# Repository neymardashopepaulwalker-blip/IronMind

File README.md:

# IronMind Macropad

Um macropad customizado com 6 switches mecânicos, encoder rotativo e display OLED, desenvolvido do zero como projeto de aprendizado em CAD, programação e design de PCB.

---

## Sobre o Projeto

Criei esse macropad para desenvolver minhas habilidades em três áreas que sempre quis dominar: design de PCB no KiCad, modelagem 3D no Fusion 360 e programação de firmware com KMK/CircuitPython. O resultado ficou muito bom, mesmo com alguns erros no caminho — e aprendi muito com cada um deles!

---

## Funcionalidades

| Tecla | Função |
|---|---|
| SW1 | Abre Claude (claude.ai) |
| SW2 | Abre Jarvis (site pessoal) |
| SW3 | Abre Discord |
| SW4 | Música anterior |
| SW5 | Play / Pause |
| SW6 | Próxima música |
| Encoder (girar) | Volume + / - |
| Encoder (pressionar) | Mute |
| OLED | Mostra volume e info |

---

## Lista de Materiais (BOM)

| Componente | Quantidade |
|---|---|
| Seeeduino XIAO RP2040 | 1x |
| Switch Cherry MX | 6x |
| Rotary Encoder EC11 | 1x |
| Display OLED 0.91" I2C | 1x |
| Diodo 1N4148 | 6x |
| Parafusos M3×16mm | 6x |
| Insertos Heatset M3×5×4mm | 4x |

---

## Estrutura do Repositório

```
IronMind/
├── README.md
├── CAD/
│   ├── Bottom.STEP
│   ├── Top.STEP
│   └── PCB.STEP
├── PCB/
│   ├── IronMind.kicad_pro
│   ├── IronMind.kicad_sch
│   └── IronMind.kicad_pcb
├── Firmware/
│   └── main.py
└── production/
    ├── gerbers.zip
    ├── Top.STEP
    ├── Bottom.STEP
    └── main.py
```

---

## Screenshots

### Esquemático

### Layout da PCB

### Caixa 3D

---

## Firmware

O firmware foi escrito em Python usando o KMK. Para instalar:

1. Instale o CircuitPython no XIAO RP2040
2. Copie a pasta `kmk` para a unidade CIRCUITPY
3. Copie o `main.py` para a unidade CIRCUITPY
4. Instale o AutoHotkey e coloque o `ironmind.ahk` na pasta Startup

---

## O que aprendi

- Design de PCB no KiCad do zero
- Modelagem 3D de caixas no Fusion 360
- Firmware com KMK e CircuitPython
- Exportação de Gerbers para fabricação (JLCPCB)

---

## Autor

[@neymardashopepaulwalker-blip](https://github.com/neymardashopepaulwalker-blip)

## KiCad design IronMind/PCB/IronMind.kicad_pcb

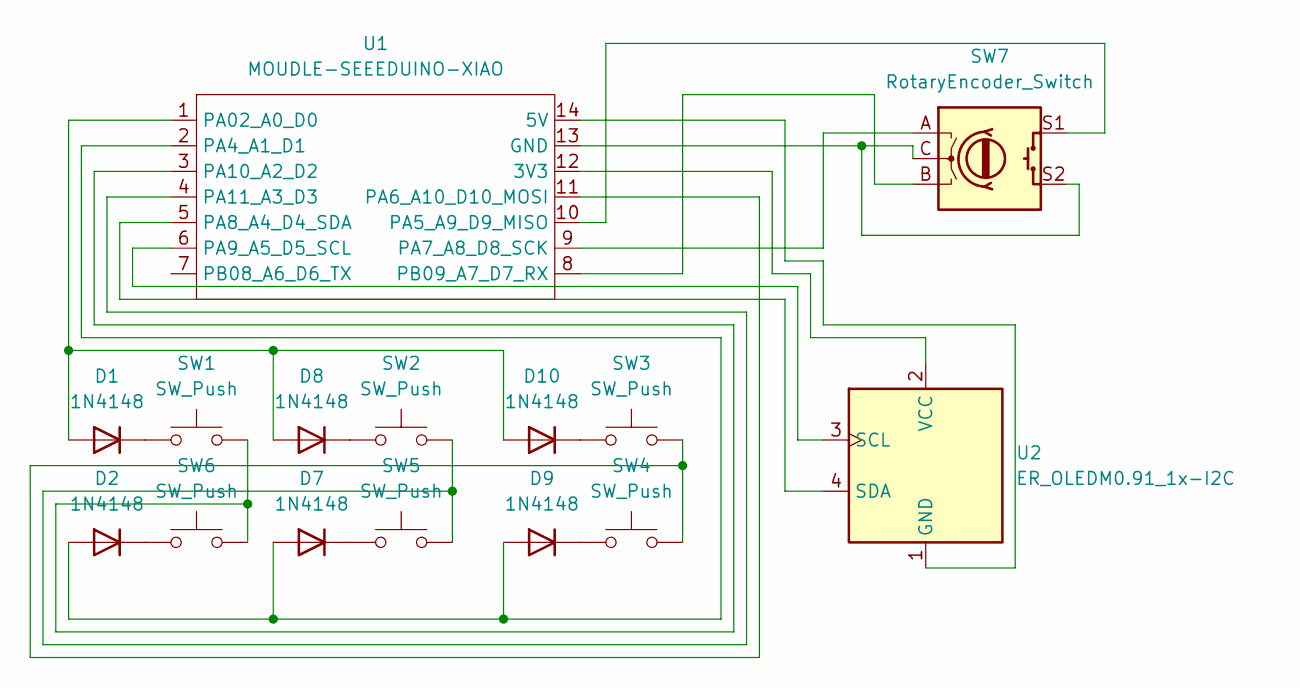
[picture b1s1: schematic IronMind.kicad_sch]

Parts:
D1, D2, D7, D8, D9, D10: 1N4148; D_DO-35_SOD27_P7.62mm_Horizontal
SW1, SW2, SW3, SW4, SW5, SW6: SW_Push; SW_Cherry_MX_1.00u_PCB
SW7: RotaryEncoder_Switch; RotaryEncoder_Alps_EC11E-Switch_Vertical_H20mm
U1: MOUDLE-SEEEDUINO-XIAO; XIAO-Generic-Hybrid-14P-2.54-21X17.8MM
U2: ER_OLEDM0.91_1x-I2C

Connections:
unnamed: D1.2 (A), D8.2 (A), D10.2 (A), U1.1 (PA02_A0_D0)
unnamed: D1.1 (K), SW1.1
unnamed: D2.2 (A), D7.2 (A), D9.2 (A), U1.2 (PA4_A1_D1)
unnamed: D2.1 (K), SW6.1
unnamed: D7.1 (K), SW5.1
unnamed: D8.1 (K), SW2.1
unnamed: D9.1 (K), SW4.1
unnamed: D10.1 (K), SW3.1
unnamed: U1.12 (3V3), U2.2 (VCC)
unnamed: U1.14 (5V), U2.1 (GND)
unnamed: SW7.C, SW7.S2, U1.13 (GND)
unnamed: SW7.S1, U1.10 (PA5_A9_D9_MISO)
unnamed: SW3.2, SW4.2, U1.11 (PA6_A10_D10_MOSI)
unnamed: SW7.A, U1.9 (PA7_A8_D8_SCK)
unnamed: U1.5 (PA8_A4_D4_SDA), U2.4 (SDA)
unnamed: U1.6 (PA9_A5_D5_SCL), U2.3 (SCL)
unnamed: SW1.2, SW6.2, U1.3 (PA10_A2_D2)
unnamed: SW2.2, SW5.2, U1.4 (PA11_A3_D3)
unnamed: SW7.B, U1.8 (PB09_A7_D7_RX)

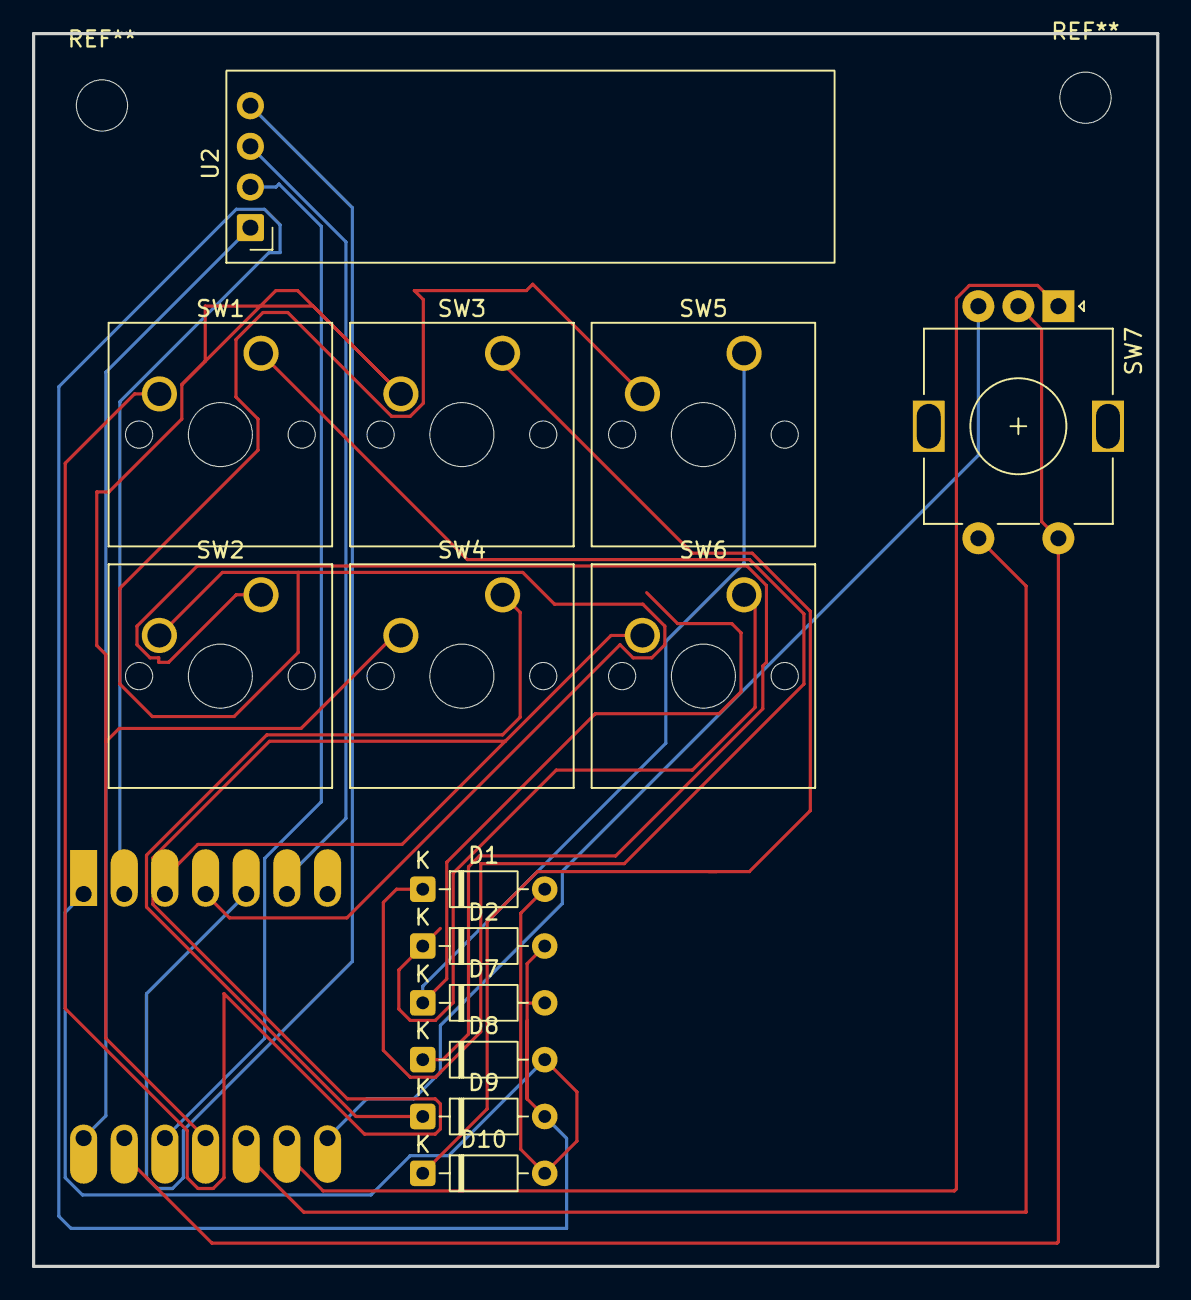
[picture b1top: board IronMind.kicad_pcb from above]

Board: 2 copper layers, 70.2 x 77.0 mm, 15 parts (1 on the bottom side), 19 nets.
